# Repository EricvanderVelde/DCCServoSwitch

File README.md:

# DCCServoSwitch
DCC railroad switch control with servo

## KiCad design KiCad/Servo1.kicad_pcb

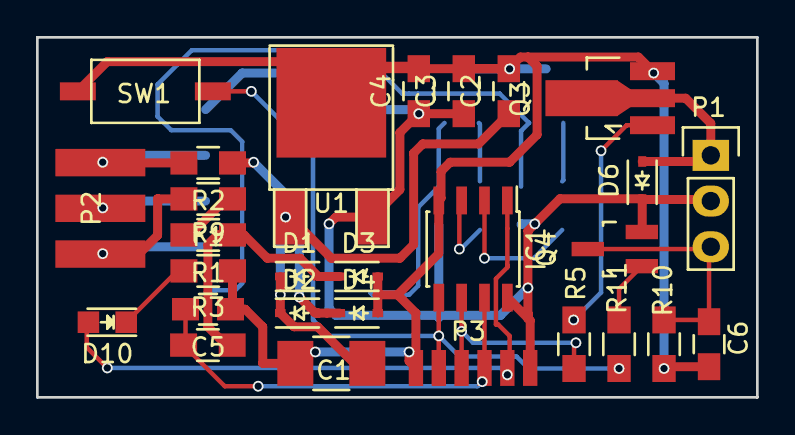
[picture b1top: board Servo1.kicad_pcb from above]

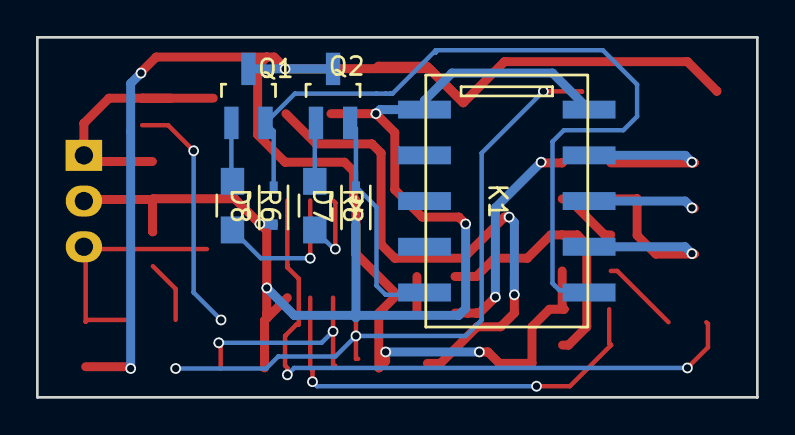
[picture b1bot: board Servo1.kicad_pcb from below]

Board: 2 copper layers, 40.0 x 20.0 mm, 35 parts (7 on the bottom side), 24 nets.

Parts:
C1: 22uF; C_1210_HandSoldering
C2, C4: 100n; C_0805_HandSoldering
C3: 330n; C_0805_HandSoldering
C5: 47p; C_0805_HandSoldering
C6: 1n; C_0805_HandSoldering
D1, D2, D3, D4, D6: D_Schottky; SOD-323
D7, D8: D; SOD-323
D10: LED; LED_0805
F1: F_Small; R_0805_HandSoldering
IC1: ATTINY45-S; SOIC-8_3.9x4.9mm_Pitch1.27mm
K1: TQ2-L2-; TQ2SA-L2
P1: CONN_01X03; Pin_Header_Straight_1x03
P2: CONN_01X03; cardedge_3p
P3: CONN_01X06; cardedge_6p_small
Q1, Q2: 2N2222; SOT-23_Handsoldering
Q3: BCX55; SOT89-3_Housing_Handsoldering
Q4: BC807; SOT-23_Handsoldering
R1, R2: 4R7; R_0805_HandSoldering
R3: 22K; R_0805_HandSoldering
R5, R6, R8, R10, R11: 1k; R_0805_HandSoldering
R9: 470R; R_0805_HandSoldering
SW1: SPST; switch_smd
U1: MC78M05CDT; TO-252-2Lead

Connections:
+5V: C3.1, C4.1, D6.1, D7.1, D8.1, IC1.8, K1.1, K1.10, P1.2, P3.6, Q4.2, U1.3
/COMMAND: C5.2, IC1.7, P3.4, R3.1
/ENABLE: IC1.6, P3.3, R5.1
/FROG: K1.3, P2.2
/RAIL_A: F1.2, K1.4, P2.3
/RAIL_B: K1.2, P2.1, R2.2
/RELAY_C1: IC1.2, R6.2
/RELAY_C2: IC1.3, R8.2
/RESET: D10.2, IC1.1, P3.5
/SERVO: IC1.5, P3.2, R11.1, SW1.1
GND: C1.2, C2.2, C3.2, C4.2, C5.1, C6.2, D3.2, D4.2, IC1.4, P3.1, Q1.3, Q2.3, Q3.3, R9.2, R10.2, SW1.2, U1.2
unnamed: C1.1, C2.1, D1.1, D2.1, U1.1
unnamed: C6.1, P1.3, Q4.3, R10.1
unnamed: D1.2, D3.1, R1.1, R3.2
unnamed: D2.2, D4.1, R2.1
unnamed: D6.2, P1.1, Q3.2
unnamed: D7.2, K1.6, Q2.2
unnamed: D8.2, K1.5, Q1.2
unnamed: D10.1, R9.1
unnamed: F1.1, R1.2
unnamed: Q1.1, R6.1
unnamed: Q2.1, R8.1
unnamed: Q3.1, R5.2
unnamed: Q4.1, R11.2
